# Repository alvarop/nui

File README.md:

# Nui

## Overview

Nui is an IR(evntually also BLE) controlled volume controller for analog audio. It sits between your audio source and speakers and can amplify or reduce the volume using IR commands (and evntually BLE).

Why do I need this, you may ask?

It all started because I have my trusty Logitech Z-2300 speakers and subwoofer I purchased back arond 2004/5. They still work great, but instead of being on my computer, they are used for my TV. Unfortunately, the TV's line out doesn't honor the TV's volume and is always outputting at max volume. Sure, I can get up and change the volume on the speakers themselves, but wouldn't it be more convenient to do it with the TV remote?!

That's how the Nui project started. It sits between my TV and my speakers and now I don't have to get up to change the volume :D

## Version 0.0.1 (Teensy version)

### Hardware
* The board files can be found [here](https://github.com/alvarop/nui/releases/tag/releases%2Fhw%2Fv0.0.1)

### Firmware
* The arduino/teensy code can be found [here](fw/teensy/nui.ino)

## Version 1.0.0 (NRF52 version)

### Hardware
* The board files can be found [here](hw/)

### Firmware
* The NRF52 code can be found [here](fw/nui/)

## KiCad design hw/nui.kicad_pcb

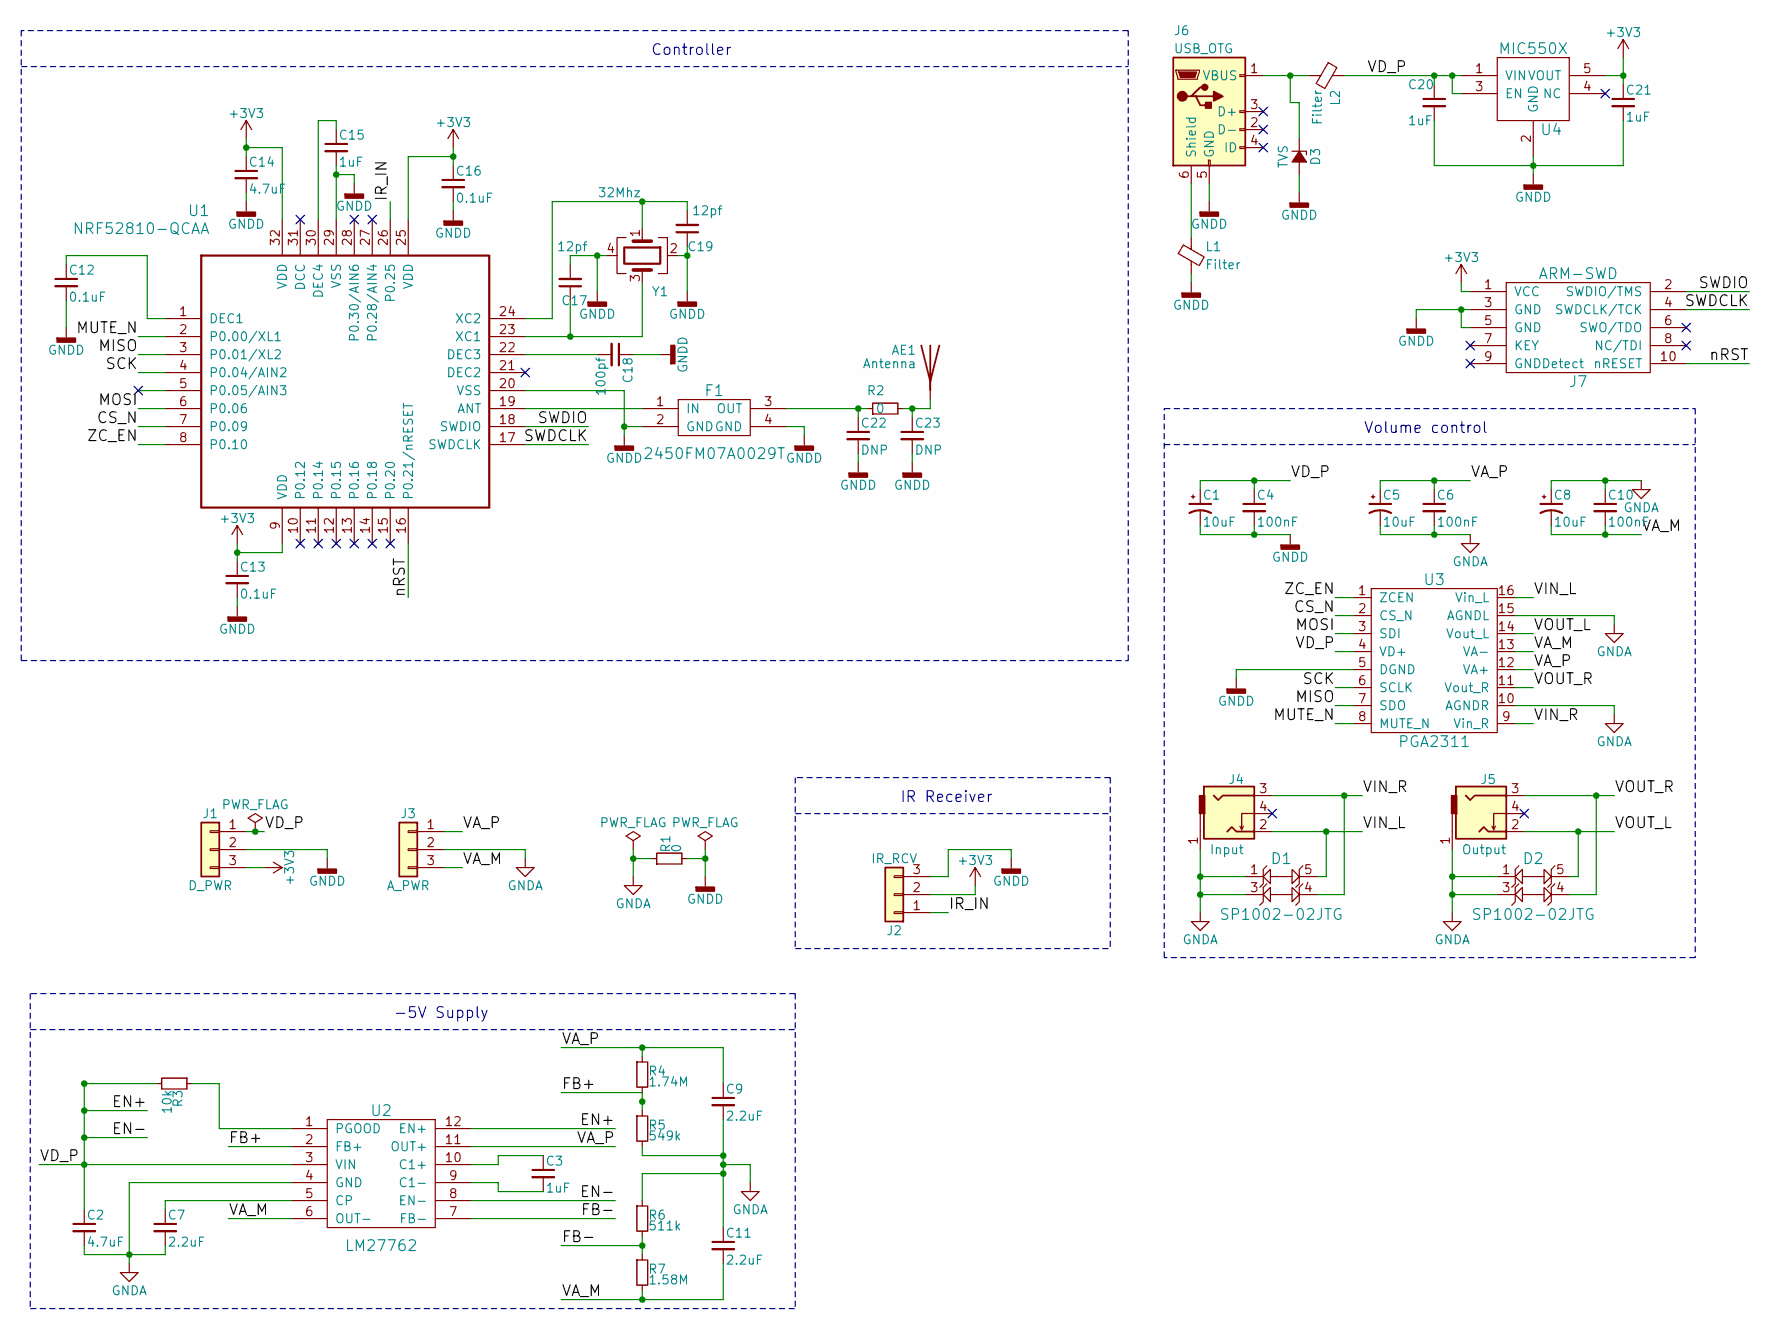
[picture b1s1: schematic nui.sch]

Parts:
AE1: Antenna; AMCA31-2R450G-S1F-T3
C1, C5, C8: 10uF; CP_Tantalum_Case-A_EIA-3216-18_Reflow; MPN F931A106MAA
C2: 4.7uF; C_0805; MPN LMK212BJ475KD-T
C3: 1uF; C_1210; MPN ECP-U1C105MA5
C4, C6, C10: 100nF; C_0603; MPN GRM188R71C104KA01D
C7: 2.2uF; C_0402_NoSilk; MPN JMK105BJ225MV-F
C9, C11: 2.2uF; C_0603; MPN C0603C225K8PACTU
C12, C13, C16: 0.1uF; C_0603
C14: 4.7uF; C_0603
C15, C20, C21: 1uF; C_0603
C17, C19: 12pf; C_0603
C18: 100pf; C_0603
C22, C23: DNP; C_0402_NoSilk
D1, D2: SP1002-02JTG; MPN SP1002-02JTG
D3: TVS; D_0603; MPN ESDA7P120-1U1M
F1: 2450FM07A0029T
J1: D_PWR; Pin_Header_Straight_1x03
J2: IR_RCV; Pin_Header_Straight_1x03; MPN TSOP2138
J3: A_PWR; Pin_Header_Straight_1x03
J4: Input; SJ-3524-SMT-TR; MPN SJ-3524-SMT-TR
J5: Output; SJ-3524-SMT-TR; MPN SJ-3524-SMT-TR
J6: USB_OTG; USB_MICRO_B
J7: ARM-SWD; ARM_SWD_SMD
L1, L2: Filter; R_0603; MPN BLM18KG221SZ1D
R1: 0; R_0603
R2: 0; R_0402_NoSilk
R3: 10k; R_0402_NoSilk; MPN CRCW040210K0JNEDC
R4: 1.74M; R_0402_NoSilk; MPN CRCW04021M74FKED
R5: 549k; R_0402_NoSilk; MPN CRCW0402549KFKED
R6: 511k; R_0402_NoSilk; MPN CRCW0402511KFKED
R7: 1.58M; R_0402_NoSilk; MPN CRCW04021M58FKED
U1: NRF52810-QCAA; NRF52810_QCAA_QFN32
U2: LM27762; MPN LM27762DSST
U3: PGA2311; PGA2311-SOIC; MPN PGA2311U
U4: MIC550X; SOT-23(M5)
Y1: 32Mhz; Crystal_SMD_2016-4pin_2.0x1.6mm

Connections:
+3V3: C13.1, C14.1, C16.1, C21.1, J1.3, J2.2, J7.1 (VCC), U1.9 (VDD), U1.25 (VDD), U1.32 (VDD), U4.5 (VOUT)
/CS_N: U1.7 (P0.09), U3.2 (CS_N)
/EN+: C1.1, C2.1, C4.1, C20.1, J1.1, L2.1, R3.2, U2.3 (VIN), U2.8 (EN-), U2.12 (EN+), U3.4 (VD+), U4.1 (VIN), U4.3 (EN)
/FB+: R4.2, R5.1, U2.2 (FB+)
/FB-: R6.2, R7.1, U2.7 (FB-)
/IR_IN: J2.1, U1.26 (P0.25)
/MISO: U1.3 (P0.01/XL2), U3.7 (SDO)
/MOSI: U1.6 (P0.06), U3.3 (SDI)
/MUTE_N: U1.2 (P0.00/XL1), U3.8 (MUTE_N)
/SCK: U1.4 (P0.04/AIN2), U3.6 (SCLK)
/SWDCLK: J7.4 (SWDCLK/TCK), U1.17 (SWDCLK)
/SWDIO: J7.2 (SWDIO/TMS), U1.18 (SWDIO)
/VA_M: C8.2, C10.2, C11.2, J3.3, R7.2, U2.6 (OUT-), U3.13 (VA-)
/VA_P: C5.1, C6.1, C9.1, J3.1, R4.1, U2.11 (OUT+), U3.12 (VA+)
/VIN_L: D1.5, J4.2, U3.16 (Vin_L)
/VIN_R: D1.4, J4.3, U3.9 (Vin_R)
/VOUT_L: D2.5, J5.2, U3.14 (Vout_L)
/VOUT_R: D2.4, J5.3, U3.11 (Vout_R)
/ZC_EN: U1.8 (P0.10), U3.1 (ZCEN)
/nRST: J7.10 (nRESET), U1.16 (P0.21/nRESET)
GNDA: C2.2, C5.2, C6.2, C7.2, C8.1, C9.2, C10.1, C11.1, D1.1, D1.3, D2.1, D2.3, J3.2, J4.1, J5.1, R1.1, R5.2, R6.1, U2.4 (GND), U3.10 (AGNDR), U3.15 (AGNDL)
GNDD: C1.2, C4.2, C12.2, C13.2, C14.2, C15.2, C16.2, C17.2, C18.1, C19.1, C20.2, C21.2, C22.2, C23.2, D3.2 (A), F1.2 (GND), F1.4 (GND), J1.2, J2.3, J6.5 (GND), J7.3 (GND), J7.5 (GND), L1.2, R1.2, U1.20 (VSS), U1.29 (VSS), U3.5 (DGND), U4.2 (GND), Y1.2, Y1.4
unnamed: AE1.1, C23.1, R2.2
unnamed: C3.1, U2.10 (C1+)
unnamed: C3.2, U2.9 (C1-)
unnamed: C7.1, U2.5 (CP)
unnamed: C12.1, U1.1 (DEC1)
unnamed: C15.1, U1.30 (DEC4)
unnamed: C17.1, U1.23 (XC1), Y1.3
unnamed: C18.2, U1.22 (DEC3)
unnamed: C19.2, U1.24 (XC2), Y1.1
unnamed: C22.1, F1.3 (OUT), R2.1
unnamed: D3.1 (K), J6.1 (VBUS), L2.2
unnamed: F1.1 (IN), U1.19 (ANT)
unnamed: J6.6 (Shield), L1.1
unnamed: R3.1, U2.1 (PGOOD)

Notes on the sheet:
Volume control
-5V Supply
Controller
IR Receiver

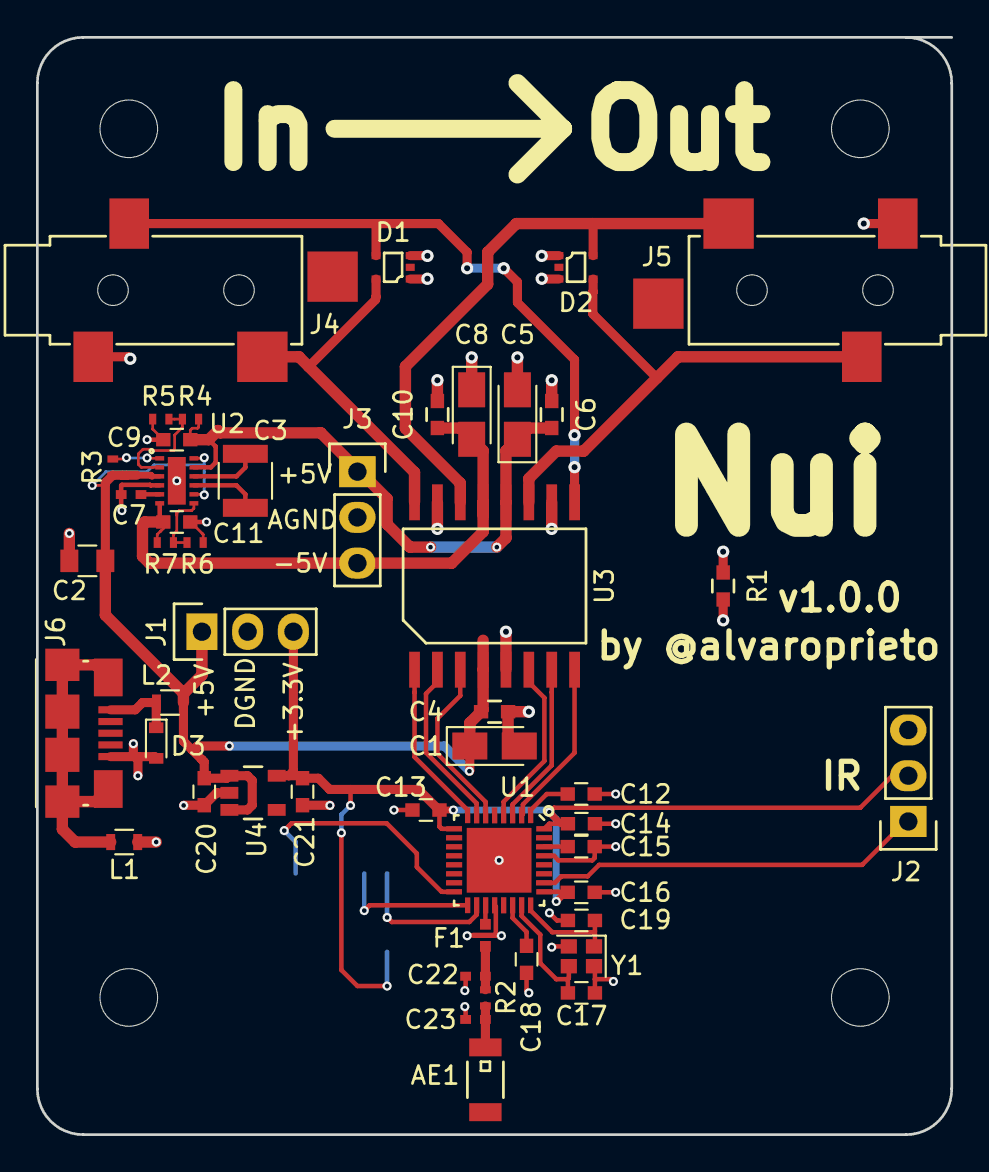
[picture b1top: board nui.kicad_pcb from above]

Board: 2 copper layers, 50.8 x 61.0 mm, 49 parts (1 on the bottom side), 36 nets.

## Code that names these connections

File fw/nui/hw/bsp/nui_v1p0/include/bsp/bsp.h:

/*
 * Licensed to the Apache Software Foundation (ASF) under one
 * or more contributor license agreements.  See the NOTICE file
 * distributed with this work for additional information
 * regarding copyright ownership.  The ASF licenses this file
 * to you under the Apache License, Version 2.0 (the
 * "License"); you may not use this file except in compliance
 * with the License.  You may obtain a copy of the License at
 *
 *  http://www.apache.org/licenses/LICENSE-2.0
 *
 * Unless required by applicable law or agreed to in writing,
 * software distributed under the License is distributed on an
 * "AS IS" BASIS, WITHOUT WARRANTIES OR CONDITIONS OF ANY
 * KIND, either express or implied.  See the License for the
 * specific language governing permissions and limitations
 * under the License.
 */

#ifndef H_BSP_H
#define H_BSP_H

#include <inttypes.h>

#include <syscfg/syscfg.h>

#ifdef __cplusplus
extern "C" {
#endif

/* Define special stackos sections */
#define sec_data_core   __attribute__((section(".data.core")))
#define sec_bss_core    __attribute__((section(".bss.core")))
#define sec_bss_nz_core __attribute__((section(".bss.core.nz")))

/* More convenient section placement macros. */
#define bssnz_t         sec_bss_nz_core

extern uint8_t _ram_start;
#define RAM_SIZE        0x10000

#define MUTE_N_PIN 0
#define MISO_PIN 1
#define SCK_PIN 4
#define MOSI_PIN 6
#define CS_N_PIN 9
#define ZC_EN_PIN 10
#define IR_IN_PIN 25

#define LED_BLINK_PIN 30

#ifdef __cplusplus
}
#endif

#endif  /* H_BSP_H */

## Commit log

2018-01-01 First draft of schematic done
2018-01-01 Footprints assigned and created
2018-01-01 Layout almost done
2018-01-02 Layout done for v0.0.1
2018-01-26 Updating power supply circuit in NUI
2018-01-26 Updated footprints and fixed swapped capacitors
2018-01-27 Start updating pcb with new design
2018-01-27 Adding teensy fw
2018-01-27 First commit of mynewt fw
2018-01-28 Start creating BSP for the nrf52810
2018-01-28 slowly changing flash map for nrf52810
2018-03-17 Get blinky up and running with tasks
2018-03-18 Update Nui 1.0.0 to use nrf52810 and LM27762
2018-03-18 Got basic IR decoding with some bugs.
    It crashes when holding the volume button... TODO...
2018-03-21 Major fw overhaul
    * Commented most of the things
    * No more blinky
    * Using 1MHz timer for data processing timeout
    * Protect IRQ/Decoding with mutex
    * Widened pulse timings to allow for error
2018-03-21 Renamed app
2018-04-04 Finally working on nui_v1p0! (IR Only)
    Requires modified apache-mynewt-core for nrf52810 support,
    currently located at:
    https://github.com/alvarop/mynewt-core/tree/nrf52810
2018-04-04 No longer need the #ifndef NRF52810 stuff on hal_i2c/spi.c
2018-04-05 Updated default volume and fixed SS bug
2018-04-06 Updating code and readme
2018-04-06 Forgot to add the photo
2018-04-06 Yargh
2018-04-07 Add some comments to teensy code
2018-04-07 Added license
